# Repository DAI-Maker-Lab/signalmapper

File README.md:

# signalmapper
signalMapper is a simple device based on a Seeeduino Stalker v3 and an Adafruit FONA 808 breakout board. signalMapper polls the cellular network associated with the SIM in the FONA for signal strength and records that strength along with the latitude and longitude of the reading. This data can then be easily uploaded to a site like cartoDB.com to generate a chloropleth or other map of cellular signal strength. The project was developed to help field teams scope sites for FONA-based sensor arrays such as the Hidrosónico. 

An Arduino with an SD card breakout board or shield could be used instead of the Stalker, though some pin changes may be necessary depending on the board.

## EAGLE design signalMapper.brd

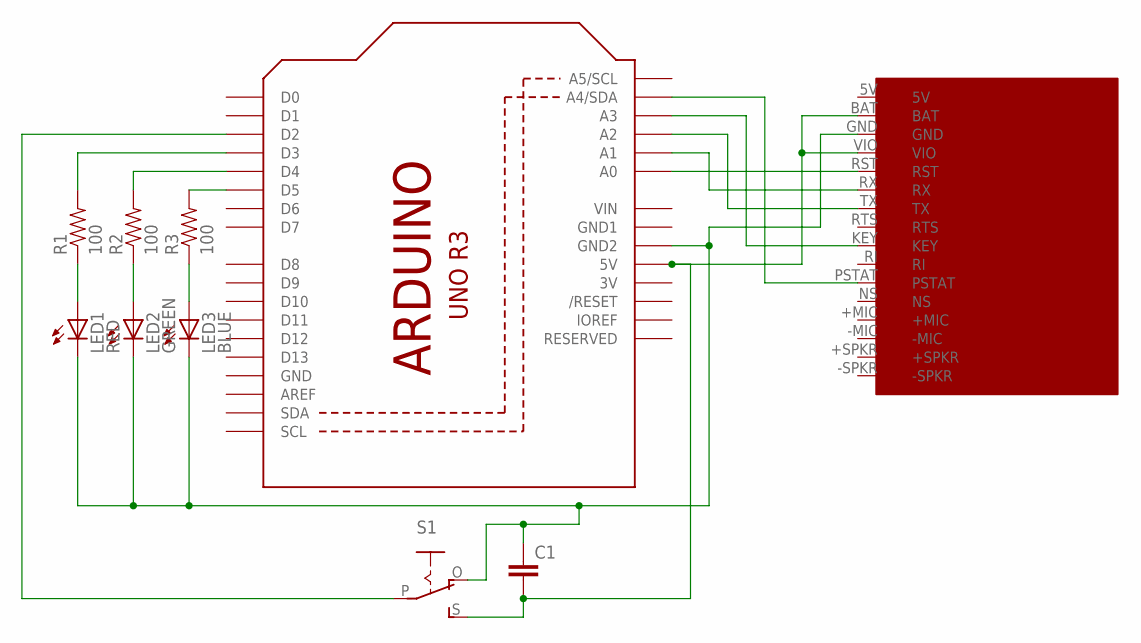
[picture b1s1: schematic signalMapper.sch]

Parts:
C1: CAPPTH; CAP-PTH-SMALL
LED1: RED; LED5MM
LED2: GREEN; LED5MM
LED3: BLUE; LED5MM
R1, R2, R3: 100; AXIAL-0.3
S1: EG1218S; EG1218
U1: ARDUINOR3-BPLACE
U$1: ADAFRUIT_FONA808

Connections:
3V: U1.3V
5V: U$1.5V
GND: U1.GND
GND1: U1.GND1
unnamed: U1.A0, U$1.RST
unnamed: U1.A1, U$1.RX
unnamed: U1.A2, U$1.TX
unnamed: U1.A3, U$1.KEY
unnamed: U1.A4 (A4/SDA), U$1.PSTAT
unnamed: C1.2, S1.S, U1.5V, U$1.BAT, U$1.VIO
unnamed: R1.P$2 (2), U1.D3
unnamed: R2.P$2 (2), U1.D4
unnamed: R3.P$2 (2), U1.D5
unnamed: LED1.A, R1.P$1 (1)
unnamed: LED2.A, R2.P$1 (1)
unnamed: LED3.A, R3.P$1 (1)
unnamed: S1.P, U1.D2
unnamed: C1.1, LED1.K (C), LED2.K (C), LED3.K (C), S1.O, U1.GND2, U$1.GND
VIN: U1.VIN

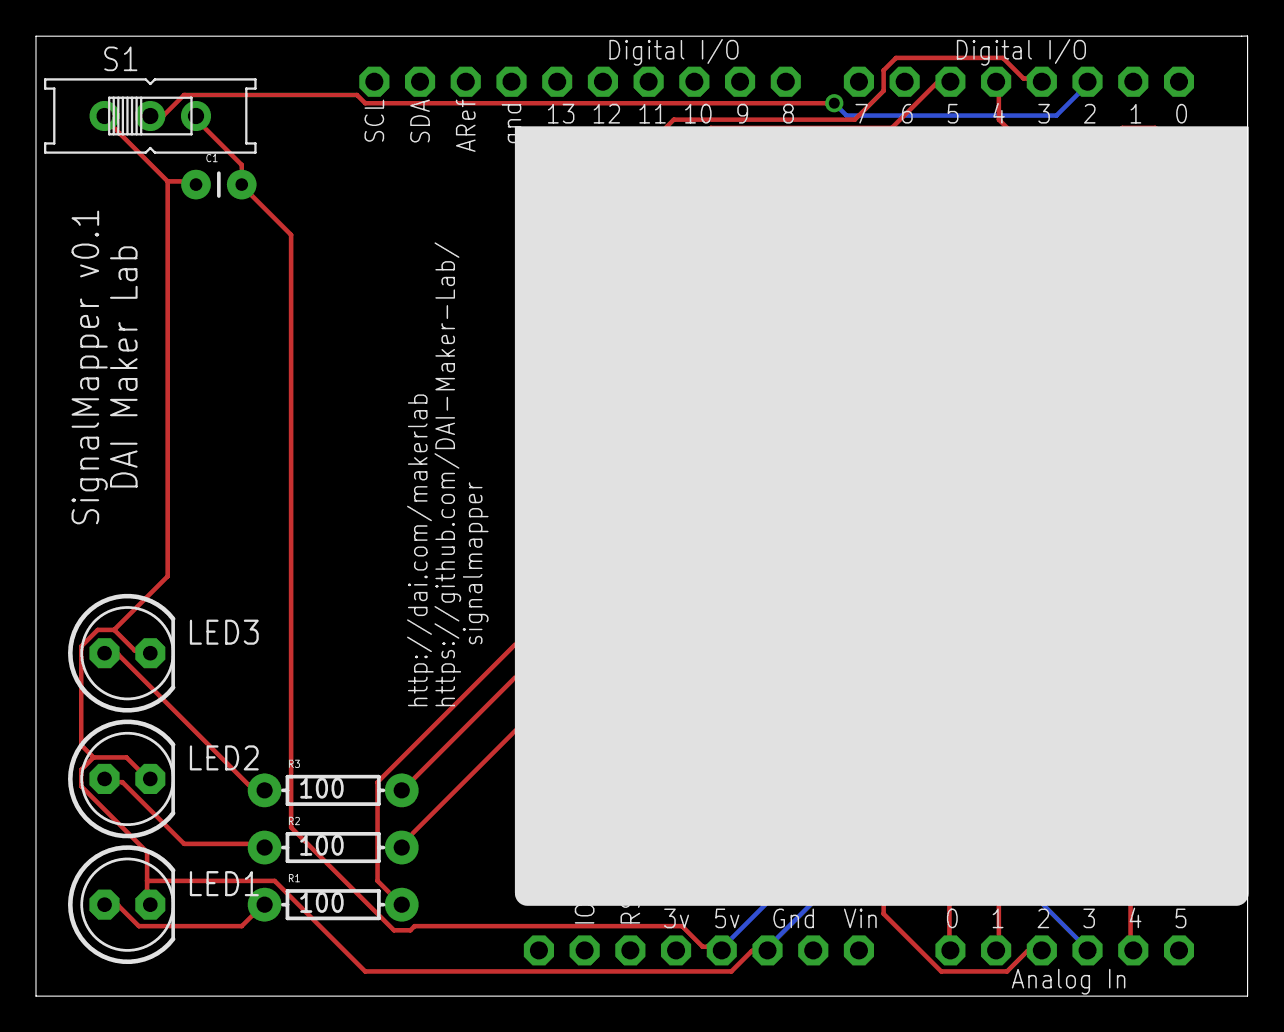
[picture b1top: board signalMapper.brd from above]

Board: 2 copper layers, 67.3 x 53.3 mm, 10 parts (0 on the bottom side), 14 nets.

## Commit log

2015-08-24 Initial file upload
    Adding the .ino and Eagle .brd and .sch files.

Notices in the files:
parts and their libraries:
SparkFun-Resistors: Licensing: Creative Commons ShareAlike 4.0 International - https://creativecommons.org/licenses/by-sa/4.0
